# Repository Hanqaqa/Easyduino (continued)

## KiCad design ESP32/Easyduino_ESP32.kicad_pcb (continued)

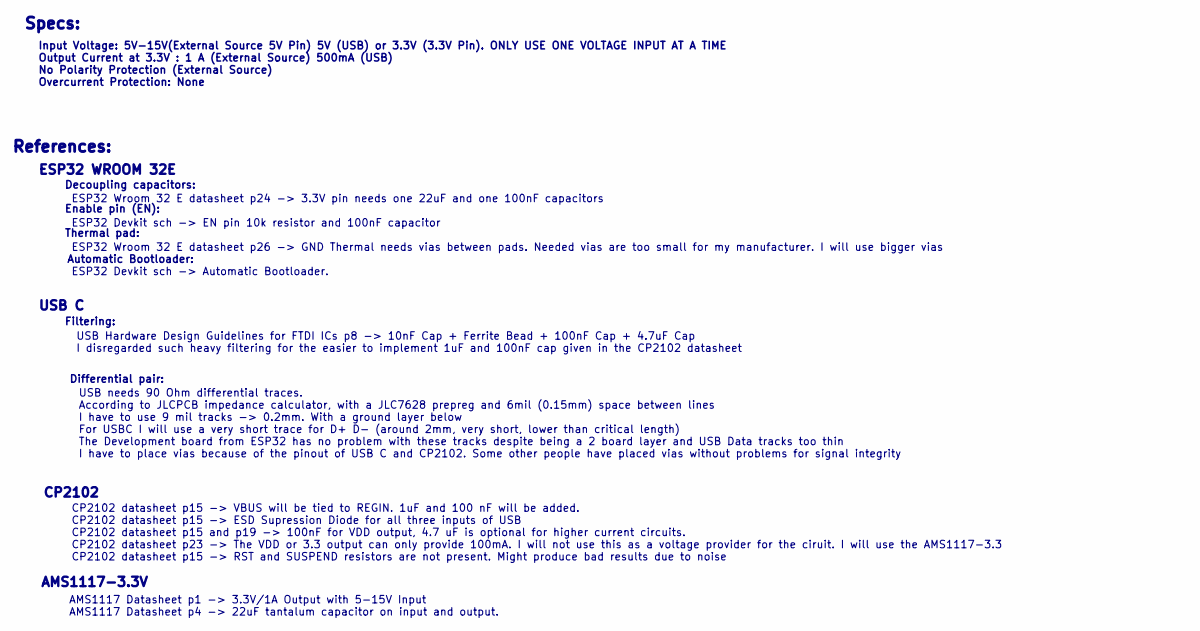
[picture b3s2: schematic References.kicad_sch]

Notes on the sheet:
ESP32 WROOM 32E
CP2102
AMS1117-3.3V
References:
Automatic Bootloader:
Decoupling capacitors:
ESP32 Wroom 32 E datasheet p24 -> 3.3V pin needs one 22uF and one 100nF capacitors ESP32 Devkit sch -> EN pin 10k resistor and 100nF capacitor ESP32 Wroom 32 E datasheet p26 -> GND Thermal needs vias between pads. Needed vias are too small for my manufacturer. I will use bigger vias ESP32 Devkit sc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
CP2102 datasheet p15 -> VBUS will be tied to REGIN. 1uF and 100 nF will be added. CP2102 datasheet p15 -> ESD Supression Diode for all three inputs of USB CP2102 datasheet p15 and p19 -> 100nF for VDD output, 4.7 uF is optional for higher current circuits. CP2102 datasheet p23 -> The VDD or 3.3 out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
Filtering:
Input Voltage: 5V-15V(External Source 5V Pin) 5V (USB) or 3.3V (3.3V Pin). ONLY USE ONE VOLTAGE INPUT AT A TIME Output Current at 3.3V : 1 A (External Source) 500mA (USB) No Polarity Protection (External Source) Overcurrent Protection: None
USB C
Specs:
Differential pair:
USB needs 90 Ohm differential traces. According to JLCPCB impedance calculator, with a JLC7628 prepreg and 6mil (0.15mm) space between lines I have to use 9 mil tracks -> 0.2mm. With a ground layer below For USBC I will use a very short trace for D+ D- (around 2mm, very short, lower than critical l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
USB Hardware Design Guidelines for FTDI ICs p8 -> 10nF Cap + Ferrite Bead + 100nF Cap + 4.7uF Cap I disregarded such heavy filtering for the easier to implement 1uF and 100nF cap given in the CP2102 datasheet
Enable pin (EN):
Thermal pad:
AMS1117 Datasheet p1 -> 3.3V/1A Output with 5-15V Input AMS1117 Datasheet p4 -> 22uF tantalum capacitor on input and output.

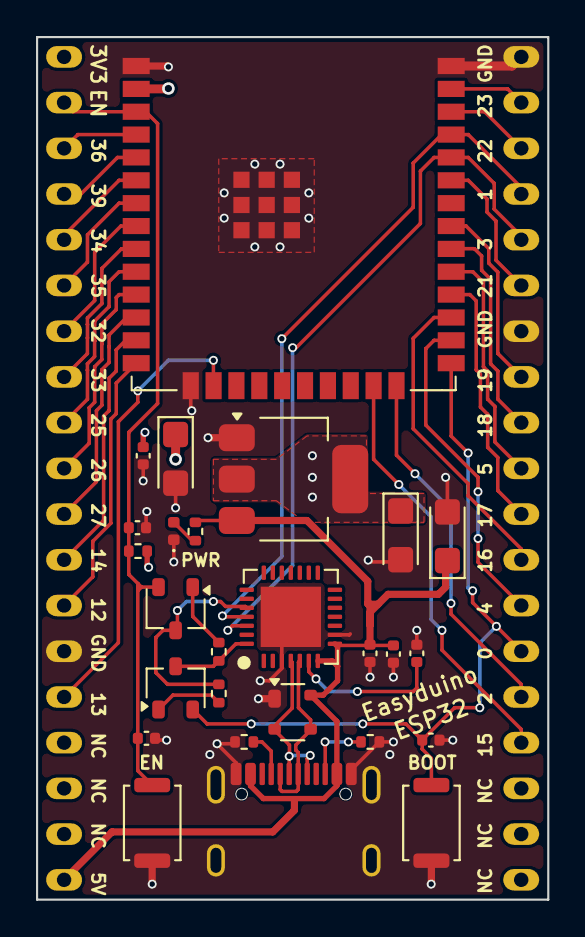
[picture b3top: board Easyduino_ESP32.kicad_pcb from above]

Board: 4 copper layers, 28.4 x 47.9 mm, 27 parts (0 on the bottom side), 40 nets.

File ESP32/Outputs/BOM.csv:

"Reference","Value","Qty","#","LCSC"
"C1","1u","1","1","C52923"
"C2","100n","1","2","C1525"
"C3","100n","1","3","C1525"
"C4","100n","1","4","C1525"
"C5","22u","1","5","C11366"
"C6","100n","1","6","C1525"
"C7","22u","1","7","C11366"
"C8","22u","1","8","C11366"
"C9","100n","1","9","C1525"
"C10","100n","1","10","C1525"
"D1","SP0503BAHT","1","11","C7074"
"D2","LED","1","12","C434447"
"J1","USB_C_Receptacle_USB2.0","1","13","C2765186"
"Q1","SS8050","1","14","C916392"
"Q2","SS8050","1","15","C916392"
"R1","10k","1","16","C25744"
"R2","5.1k","1","17","C25905"
"R3","5.1k","1","18","C25905"
"R4","10k","1","19","C25744"
"R5","10k","1","20","C25744"
"R6","2k","1","21","C4109"
"SW1","SW_Push","1","22","C720477"
"SW2","SW_Push","1","23","C720477"
"U1","CP2102N-Axx-xQFN28","1","24","C6568"
"U2","ESP32-WROOM-E","1","25","C701342"
"U3","AMS1117-3.3","1","26","C6186"
"U4","ESP32-DevKitC","1","27","-"

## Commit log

2026-04-20 Added TODO: Fix ESP32 and ESP32S3 flash and reset bugs
    Updated to-do list with fixes for ESP32 and ESP32S3.
2026-04-21 ESP32 CP2102 bugfix
2026-04-21 ESP32S3 CP2102 bugfix
2026-04-21 Changed TODO: Order ESP32S3
2026-04-27 Added .step files and fixed Jobset
2026-04-28 Mention CPL JLCPCBs fix in readme.md
2026-05-27 Announce new PCBs
2026-05-27 RP2040 v1.2
2026-05-27 ESP32S3 v1.2
2026-05-27 RP2040 v1.2 SilkScreen Fix
